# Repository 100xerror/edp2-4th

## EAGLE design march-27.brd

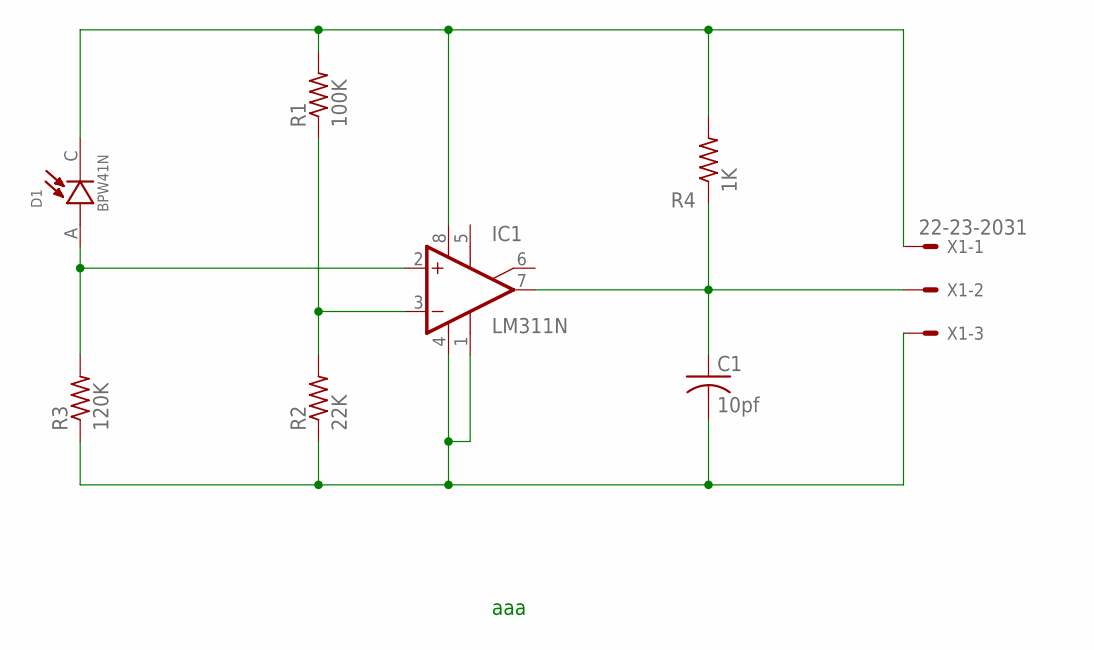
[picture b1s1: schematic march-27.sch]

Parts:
C1: 10pf; C025-024X044
D1: BPW41N; DIO_BPW41N
IC1: LM311N; DIL08
R1: 100K; 0204/5
R2: 22K; 0204/5
R3: 120K; 0204/5
R4: 1K; 0204/5
X1: 22-23-2031

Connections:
unnamed: D1.C, IC1.8 (V+), R1.2, R4.2, X1.1
unnamed: IC1.3 (-IN), R1.1, R2.2
unnamed: C1.2, IC1.1 (GND), IC1.4 (V-), R2.1, R3.1, X1.3
unnamed: D1.A, IC1.2 (+IN), R3.2
unnamed: C1.1, IC1.7 (OUT), R4.1, X1.2

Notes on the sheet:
aaa

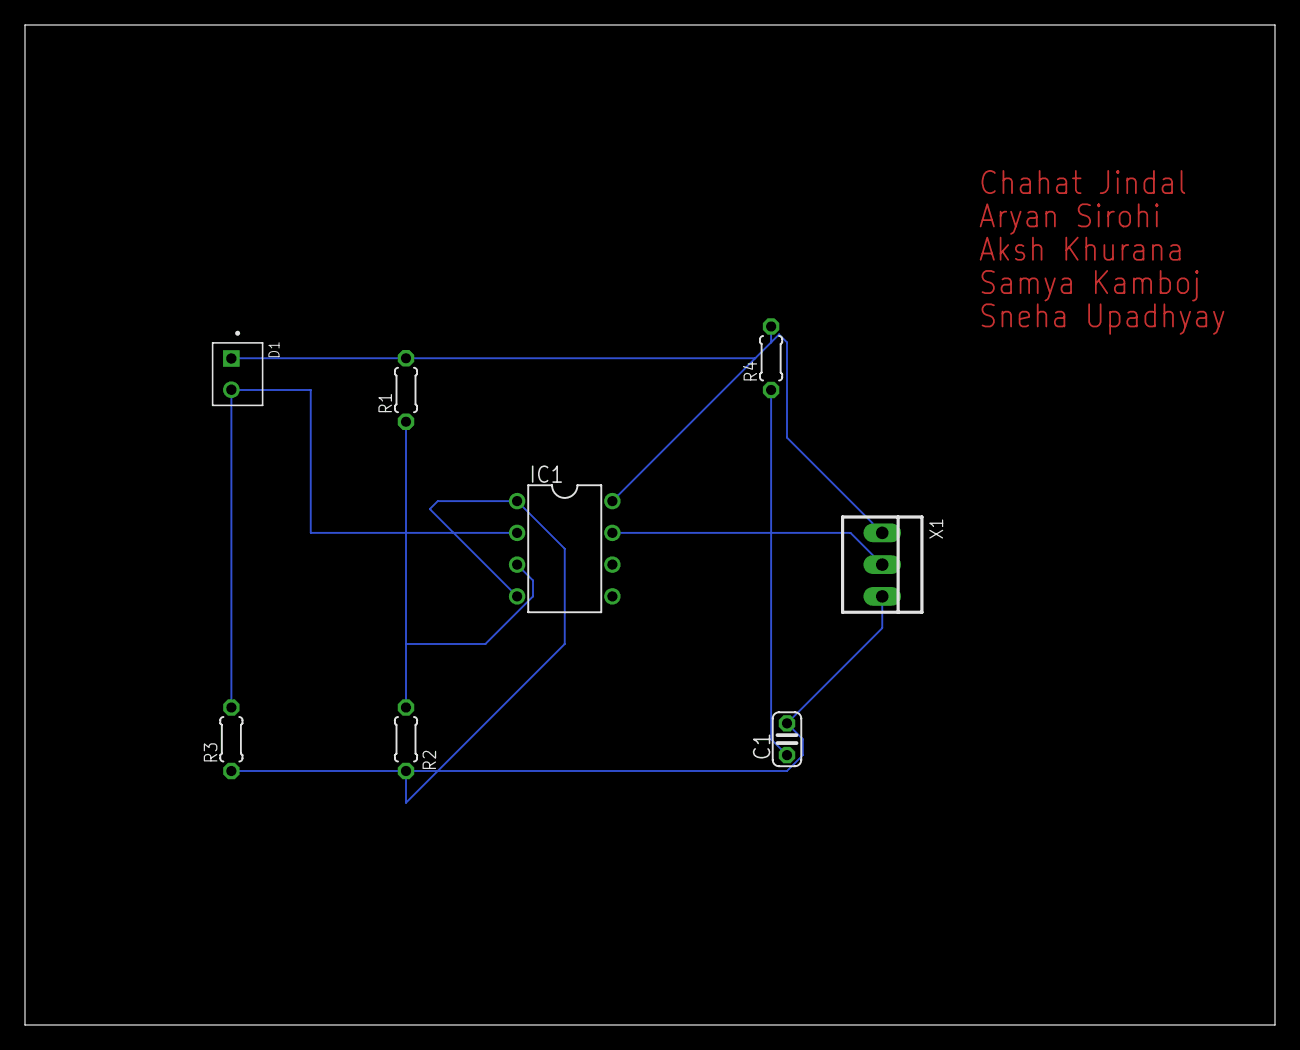
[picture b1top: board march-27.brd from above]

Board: 2 copper layers, 100.0 x 80.0 mm, 8 parts (0 on the bottom side), 5 nets.
